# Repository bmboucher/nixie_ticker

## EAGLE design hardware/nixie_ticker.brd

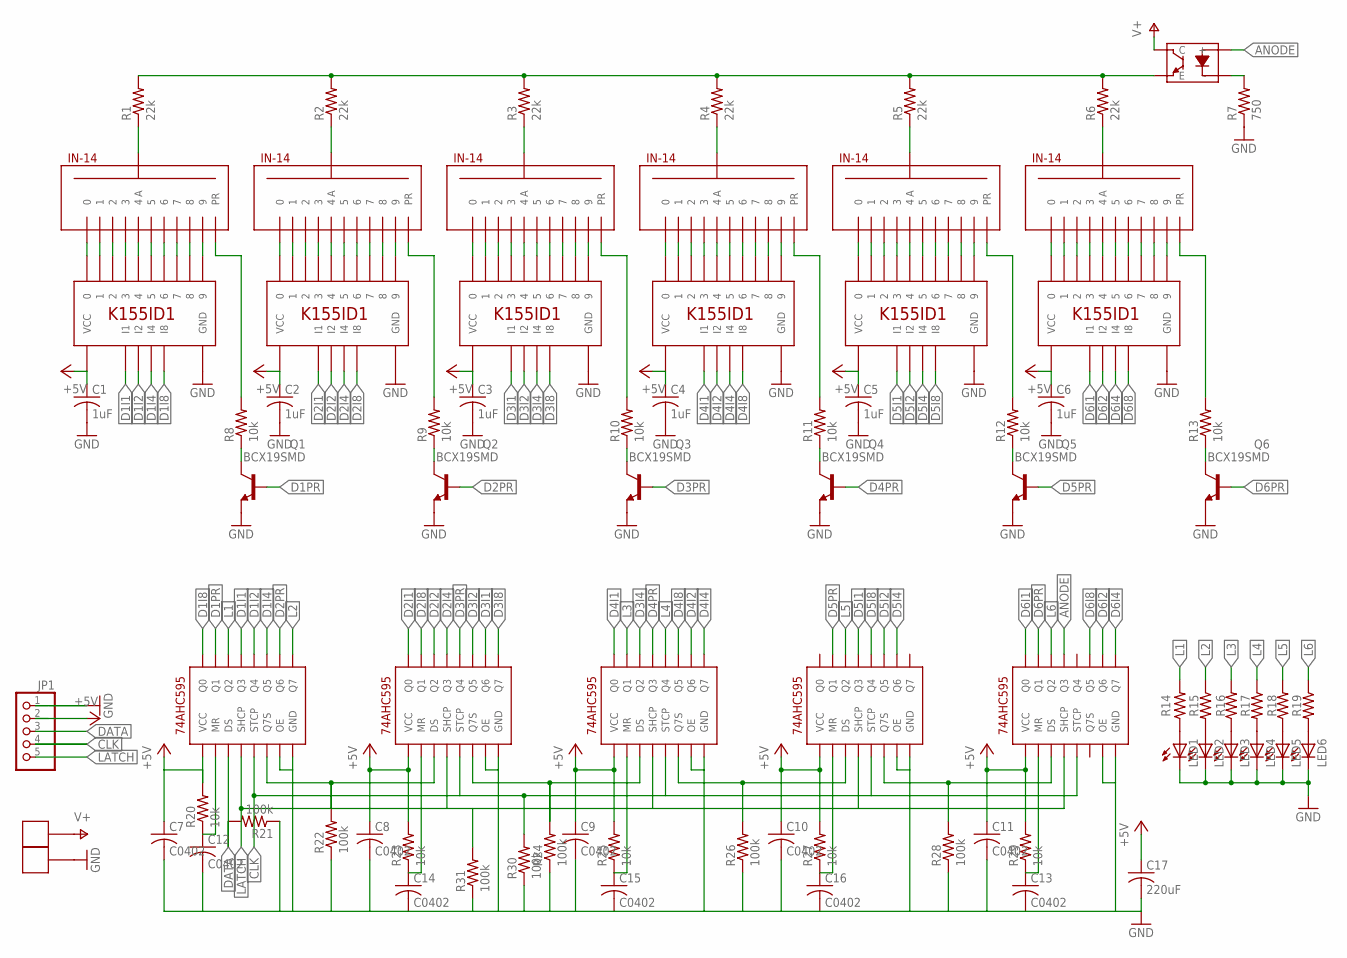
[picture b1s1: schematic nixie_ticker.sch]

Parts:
C1, C2, C3, C4, C5, C6: 1uF; C0402
C7, C8, C9, C10, C11, C12, C13, C14, C15, C16: C0402
C17: 220uF; CAPAE830X1050
JP1: PINHD-1X5; 1X05
JP2, JP3: ZKFDS
LED1, LED2, LED3, LED4, LED5, LED6: LEDCHIP-LED0603; CHIP-LED0603
N1, N2, N3, N4, N5, N6: IN14_12PIN12PIN; IN14-12PIN
Q1, Q2, Q3, Q4, Q5, Q6: BCX19SMD; SOT23-BEC
R1, R2, R3, R4, R5, R6: 22k; R1206
R7: 750; R0603
R8, R9, R10, R11, R12, R13: 10k; R0805
R14, R15, R16, R17, R18, R19: R-US_R0805; R0805
R20, R23, R25, R27, R29: 10k; R0402
R21, R22, R24, R26, R28, R30, R31: 100k; R0402
U1: TLP3873D; SOP254P1000X215-4
U2, U3, U4, U5, U6, U7: K155ID1; DIP-16_SMD
U8, U9, U10, U11, U12: 74AHC595; 16SOIC

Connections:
+5V: C1.1 (+), C2.1 (+), C3.1 (+), C4.1 (+), C5.1 (+), C6.1 (+), C7.1 (+), C8.1 (+), C9.1 (+), C10.1 (+), C11.1 (+), C17.1 (+), JP1.2, R20.2, R23.2, R25.2, R27.2, R29.2, U2.P$5 (VCC), U3.P$5 (VCC), U4.P$5 (VCC), U5.P$5 (VCC), U6.P$5 (VCC), U7.P$5 (VCC), U8.P$16 (VCC), U9.P$16 (VCC), U10.P$16 (VCC), U11.P$16 (VCC), U12.P$16 (VCC)
ANODE: U1.1 (+), U12.P$3 (Q3)
CLK: JP1.4, R30.2, U8.P$12 (STCP), U9.P$12 (STCP), U10.P$12 (STCP), U11.P$12 (STCP), U12.P$12 (STCP)
D1I1: U2.P$3 (I1), U8.P$3 (Q3)
D1I2: U2.P$6 (I2), U8.P$4 (Q4)
D1I4: U2.P$7 (I4), U8.P$5 (Q5)
D1I8: U2.P$4 (I8), U8.P$15 (Q0)
D1PR: Q1.B, U8.P$1 (Q1)
D2I1: U3.P$3 (I1), U9.P$15 (Q0)
D2I2: U3.P$6 (I2), U9.P$2 (Q2)
D2I4: U3.P$7 (I4), U9.P$3 (Q3)
D2I8: U3.P$4 (I8), U9.P$1 (Q1)
D2PR: Q2.B, U8.P$6 (Q6)
D3I1: U4.P$3 (I1), U9.P$6 (Q6)
D3I2: U4.P$6 (I2), U9.P$5 (Q5)
D3I4: U4.P$7 (I4), U10.P$2 (Q2)
D3I8: U4.P$4 (I8), U9.P$7 (Q7)
D3PR: Q3.B, U9.P$4 (Q4)
D4I1: U5.P$3 (I1), U10.P$15 (Q0)
D4I2: U5.P$6 (I2), U10.P$6 (Q6)
D4I4: U5.P$7 (I4), U10.P$7 (Q7)
D4I8: U5.P$4 (I8), U10.P$5 (Q5)
D4PR: Q4.B, U10.P$3 (Q3)
D5I1: U6.P$3 (I1), U11.P$3 (Q3)
D5I2: U6.P$6 (I2), U11.P$5 (Q5)
D5I4: U6.P$7 (I4), U11.P$6 (Q6)
D5I8: U6.P$4 (I8), U11.P$4 (Q4)
D5PR: Q5.B, U11.P$1 (Q1)
D6I1: U7.P$3 (I1), U12.P$15 (Q0)
D6I2: U7.P$6 (I2), U12.P$6 (Q6)
D6I4: U7.P$7 (I4), U12.P$7 (Q7)
D6I8: U7.P$4 (I8), U12.P$5 (Q5)
D6PR: Q6.B, U12.P$1 (Q1)
DATA: JP1.3, R21.2, U8.P$14 (DS)
GND: C1.2 (-), C2.2 (-), C3.2 (-), C4.2 (-), C5.2 (-), C6.2 (-), C7.2 (-), C8.2 (-), C9.2 (-), C10.2 (-), C11.2 (-), C12.2 (-), C13.2 (-), C14.2 (-), C15.2 (-), C16.2 (-), C17.2 (-), JP1.1, JP3.P$1, JP3.P$2, LED1.C, LED2.C, LED3.C, LED4.C, LED5.C, LED6.C, Q1.E, Q2.E, Q3.E, Q4.E, Q5.E, Q6.E, R7.1, R21.1, R22.1, R24.1, R26.1, R28.1, R30.1, R31.1, U2.P$12 (GND), U3.P$12 (GND), U4.P$12 (GND), U5.P$12 (GND), U6.P$12 (GND), U7.P$12 (GND), U8.P$8 (GND), U8.P$13 (OE), U9.P$8 (GND), U9.P$13 (OE), U10.P$8 (GND), U10.P$13 (OE), U11.P$8 (GND), U11.P$13 (OE), U12.P$8 (GND), U12.P$13 (OE)
L1: R14.2, U8.P$2 (Q2)
L2: R15.1, U8.P$7 (Q7)
L3: R16.2, U10.P$1 (Q1)
L4: R17.1, U10.P$4 (Q4)
L5: R18.2, U11.P$2 (Q2)
L6: R19.1, U12.P$2 (Q2)
LATCH: JP1.5, R31.2, U8.P$11 (SHCP), U9.P$11 (SHCP), U10.P$11 (SHCP), U11.P$11 (SHCP), U12.P$11 (SHCP)
unnamed: N1.P$12 (0), U2.P$16 (0)
unnamed: N1.P$3 (1), U2.P$15 (1)
unnamed: N1.P$4 (2), U2.P$8 (2)
unnamed: N1.P$5 (3), U2.P$9 (3)
unnamed: N1.P$6 (4), U2.P$13 (4)
unnamed: N1.P$7 (5), U2.P$14 (5)
unnamed: N1.P$8 (6), U2.P$11 (6)
unnamed: N1.P$9 (7), U2.P$10 (7)
unnamed: N1.P$10 (8), U2.P$1 (8)
unnamed: N1.P$11 (9), U2.P$2 (9)
unnamed: N2.P$12 (0), U3.P$16 (0)
unnamed: N2.P$3 (1), U3.P$15 (1)
unnamed: N2.P$4 (2), U3.P$8 (2)
unnamed: N2.P$5 (3), U3.P$9 (3)
unnamed: N2.P$6 (4), U3.P$13 (4)
unnamed: N2.P$7 (5), U3.P$14 (5)
unnamed: N2.P$8 (6), U3.P$11 (6)
unnamed: N2.P$9 (7), U3.P$10 (7)
unnamed: N2.P$10 (8), U3.P$1 (8)
unnamed: N2.P$11 (9), U3.P$2 (9)
unnamed: R24.2, U9.P$9 (Q7S), U10.P$14 (DS)
unnamed: R22.2, U8.P$9 (Q7S), U9.P$14 (DS)
unnamed: R26.2, U10.P$9 (Q7S), U11.P$14 (DS)
unnamed: R28.2, U11.P$9 (Q7S), U12.P$14 (DS)
unnamed: LED2.A, R15.2
unnamed: C13.1 (+), R29.1, U12.P$10 (MR)
unnamed: LED3.A, R16.1
unnamed: LED1.A, R14.1
unnamed: LED4.A, R17.2
unnamed: N3.P$12 (0), U4.P$16 (0)
unnamed: N3.P$3 (1), U4.P$15 (1)
unnamed: N3.P$4 (2), U4.P$8 (2)
unnamed: N3.P$5 (3), U4.P$9 (3)
unnamed: N3.P$6 (4), U4.P$13 (4)
unnamed: N3.P$7 (5), U4.P$14 (5)
unnamed: N3.P$8 (6), U4.P$11 (6)
unnamed: N3.P$9 (7), U4.P$10 (7)
unnamed: N3.P$10 (8), U4.P$1 (8)
unnamed: N3.P$11 (9), U4.P$2 (9)
unnamed: LED5.A, R18.1
unnamed: LED6.A, R19.2
unnamed: N1.P$2 (PR), R8.2
unnamed: Q1.C, R8.1
unnamed: N3.P$2 (PR), R10.2
unnamed: Q3.C, R10.1
unnamed: N5.P$2 (PR), R12.2
unnamed: Q5.C, R12.1
unnamed: N6.P$2 (PR), R13.2
unnamed: Q6.C, R13.1
unnamed: N1.P$1 (A), R1.1
unnamed: N4.P$12 (0), U5.P$16 (0)
unnamed: N4.P$3 (1), U5.P$15 (1)
unnamed: N4.P$4 (2), U5.P$8 (2)
unnamed: N4.P$5 (3), U5.P$9 (3)
unnamed: N4.P$6 (4), U5.P$13 (4)
unnamed: N4.P$7 (5), U5.P$14 (5)
unnamed: N4.P$8 (6), U5.P$11 (6)
unnamed: N4.P$9 (7), U5.P$10 (7)
unnamed: N4.P$10 (8), U5.P$1 (8)
unnamed: N4.P$11 (9), U5.P$2 (9)
unnamed: N5.P$1 (A), R5.1
unnamed: N5.P$12 (0), U6.P$16 (0)
unnamed: N5.P$3 (1), U6.P$15 (1)
unnamed: N5.P$4 (2), U6.P$8 (2)
unnamed: N5.P$5 (3), U6.P$9 (3)
unnamed: N5.P$6 (4), U6.P$13 (4)
unnamed: N5.P$7 (5), U6.P$14 (5)
unnamed: N5.P$8 (6), U6.P$11 (6)
unnamed: N5.P$9 (7), U6.P$10 (7)
unnamed: N5.P$10 (8), U6.P$1 (8)
unnamed: N5.P$11 (9), U6.P$2 (9)
unnamed: R1.2, R2.2, R3.2, R4.2, R5.2, R6.2, U1.3 (E)
unnamed: R7.2, U1.2 (-)
unnamed: N6.P$1 (A), R6.1
unnamed: N2.P$1 (A), R2.1
unnamed: C14.1 (+), R23.1, U9.P$10 (MR)
unnamed: C12.1 (+), R20.1, U8.P$10 (MR)
unnamed: C15.1 (+), R25.1, U10.P$10 (MR)
unnamed: C16.1 (+), R27.1, U11.P$10 (MR)
unnamed: N3.P$1 (A), R3.1
unnamed: N6.P$12 (0), U7.P$16 (0)
unnamed: N6.P$3 (1), U7.P$15 (1)
unnamed: N6.P$4 (2), U7.P$8 (2)
unnamed: N6.P$5 (3), U7.P$9 (3)
unnamed: N6.P$6 (4), U7.P$13 (4)
unnamed: N6.P$7 (5), U7.P$14 (5)
unnamed: N6.P$8 (6), U7.P$11 (6)
unnamed: N6.P$9 (7), U7.P$10 (7)
unnamed: N6.P$10 (8), U7.P$1 (8)
unnamed: N6.P$11 (9), U7.P$2 (9)
unnamed: N4.P$1 (A), R4.1
unnamed: Q2.C, R9.1
unnamed: Q4.C, R11.1
unnamed: N4.P$2 (PR), R11.2
unnamed: N2.P$2 (PR), R9.2
V+: JP2.P$1, JP2.P$2, U1.4 (C)

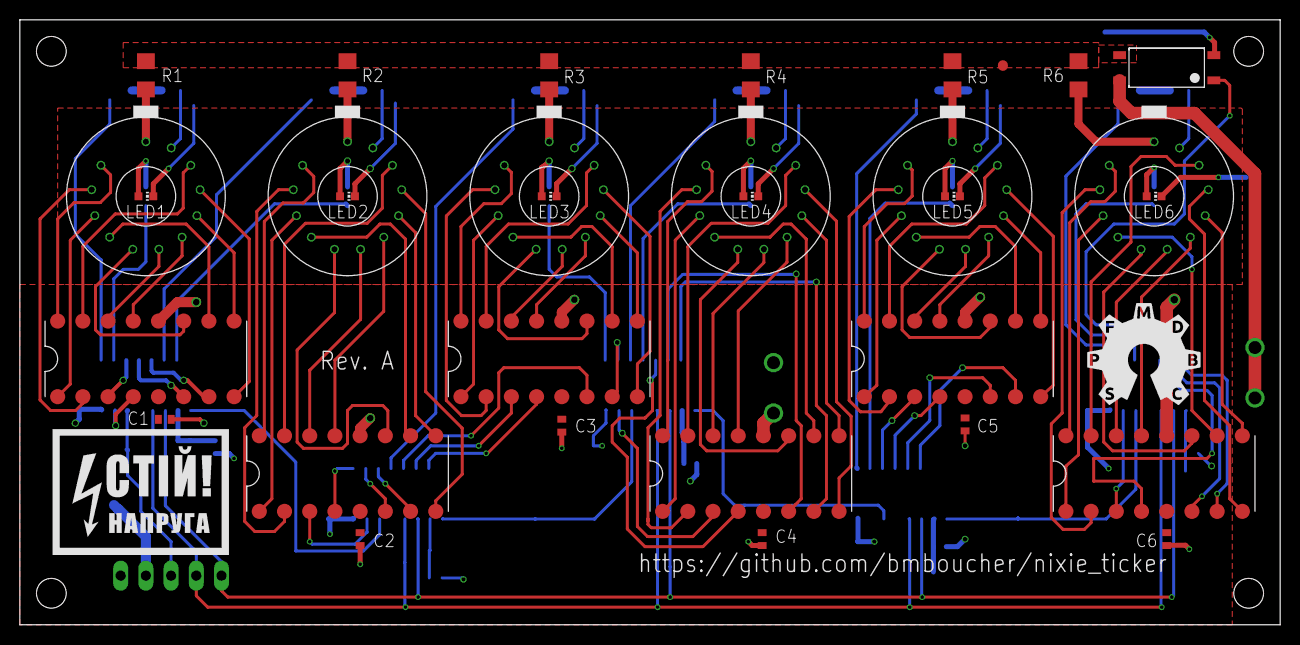
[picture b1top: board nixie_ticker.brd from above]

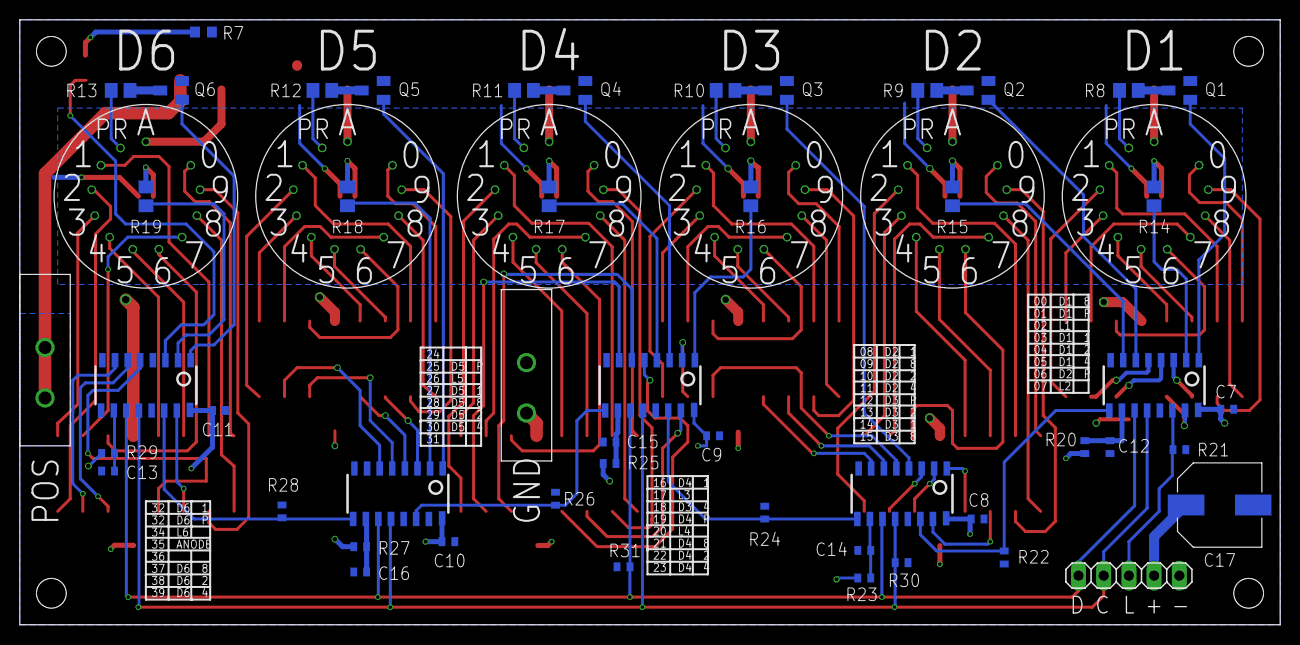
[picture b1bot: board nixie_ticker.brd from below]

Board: 2 copper layers, 127.0 x 61.0 mm, 81 parts (50 on the bottom side), 138 nets.

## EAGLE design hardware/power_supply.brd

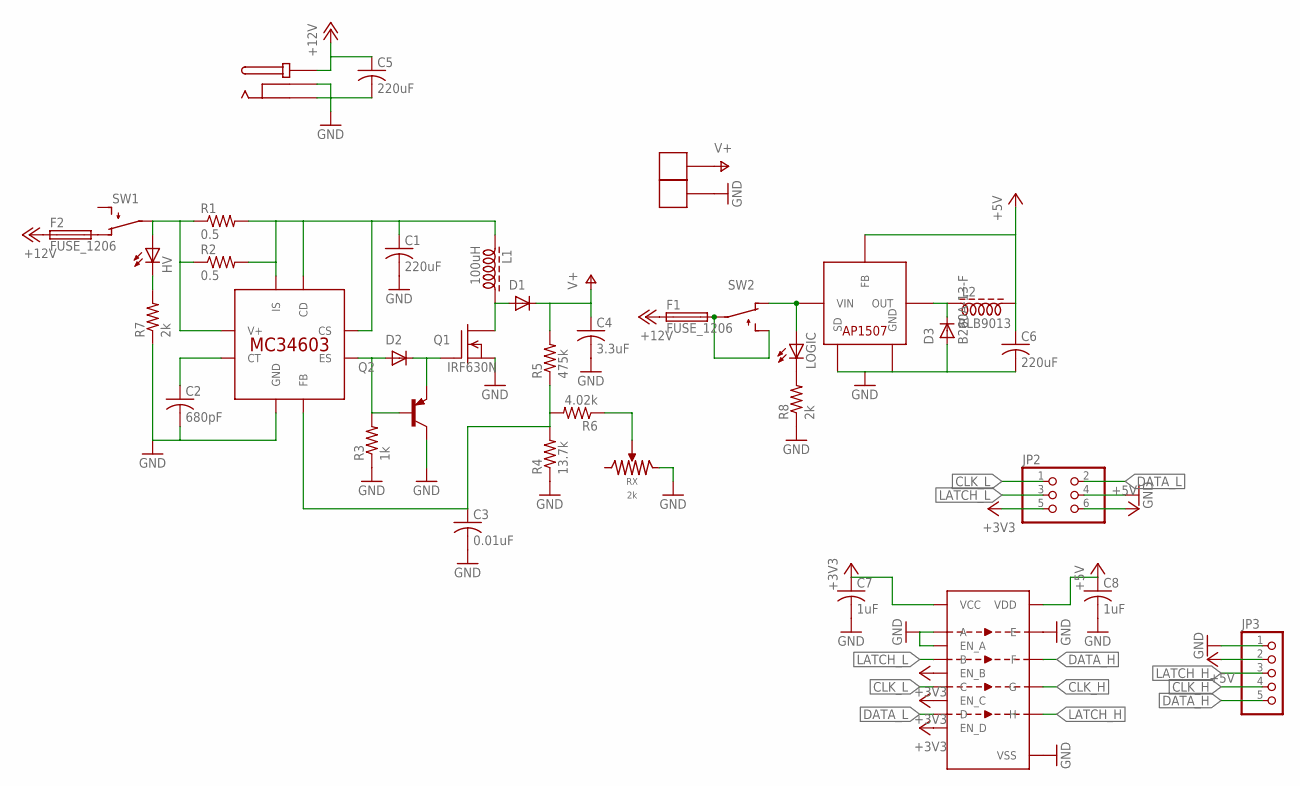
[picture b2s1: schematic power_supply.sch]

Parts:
C1, C5, C6: 220uF; CAPAE830X1050
C2: 680pF; C0402
C3: 0.01uF; C0402
C4: 3.3uF; CAPAE830X1050
C7, C8: 1uF; C0402
D1: BAV21W; SOD3616X115
D2: MMBD914L; SOT23
D3: B260A-13-F; DIOM4326X230
F1, F2: FUSE_1206; R1206
HV: LEDCHIP-LED0805; CHIP-LED0805
JP2: PINHD-2X3; 2X03
JP3: PINHD-1X5; 1X05
L1: 100uH; RLB9012
L2: RLB9013
LOGIC: LEDCHIP-LED0805; CHIP-LED0805
Q1: IRF630N; TO254P1524X483-3
Q2: BC807-16-PNP-SOT23-BEC; SOT23-BEC
R1, R2: 0.5; R1206
R3: 1k; R0805
R4: 13.7k; R1206
R5: 475k; R1206
R6: 4.02k; R1206
R7, R8: 2k; R0805
RX: 2k; TC33X-2
SW1, SW2: T411001B
U1: MC34063; SOIC127P600X175-8
U2: AP1507SOIC-8; SOIC127P600X175-8
U3: CD40109B_SPLITEN; SOP65P640X120-16
U$1: EJ508A
U$5, U$6: ZKFDS

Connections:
+3V3: C7.1 (+), JP2.5, U3.1 (VCC), U3.7 (EN_B), U3.9 (EN_C), U3.15 (EN_D)
+5V: C6.1 (+), C8.1 (+), JP2.6, JP3.2, L2.P$2 (2), U2.3 (FB), U3.16 (VDD)
+12V: C5.1 (+), F1.1, F2.1, U$1.P$1
CLK_H: JP3.4, U3.11 (G)
CLK_L: JP2.1, U3.10 (C)
DATA_H: JP3.5, U3.5 (F)
DATA_L: JP2.2, U3.14 (D)
GND: C1.2 (-), C2.2 (-), C3.2 (-), C4.2 (-), C5.2 (-), C6.2 (-), C7.2 (-), C8.2 (-), D3.2 (A), JP2.4, JP3.1, Q1.2 (S), Q2.C, R3.1, R4.1, R7.1, R8.1, RX.P$3, U1.4 (GND), U2.4 (SD), U2.5 (GND), U2.6 (GND), U2.7 (GND), U2.8 (GND), U3.2 (EN_A), U3.3 (A), U3.4 (E), U3.8 (VSS), U3.12 (VSS), U$1.P$2, U$1.P$3, U$6.P$1, U$6.P$2
LATCH_H: JP3.3, U3.13 (H)
LATCH_L: JP2.3, U3.6 (B)
unnamed: C1.1 (+), L1.P$1 (1), R1.2, R2.2, U1.1 (CS), U1.7 (IS), U1.8 (CD)
unnamed: D1.1 (A), L1.P$2 (2), Q1.3 (D)
unnamed: R6.1, RX.P$2
unnamed: D2.1 (A), Q2.B, R3.2, U1.2 (ES)
unnamed: D2.3 (C), Q1.1 (G), Q2.E
unnamed: HV.A, R1.1, R2.1, SW1.P$2 (2), U1.6 (V+)
unnamed: C2.1 (+), U1.3 (CT)
unnamed: LOGIC.A, SW2.P$1 (1), U2.1 (VIN)
unnamed: C3.1 (+), R4.2, R5.1, R6.2, U1.5 (FB)
unnamed: D3.1 (C), L2.P$1 (1), U2.2 (OUT)
unnamed: HV.C, R7.2
unnamed: LOGIC.C, R8.2
unnamed: F1.2, SW2.P$2 (2), SW2.P$3 (3)
unnamed: F2.2, SW1.P$1 (1)
V+: C4.1 (+), D1.2 (C), R5.2, U$5.P$1, U$5.P$2

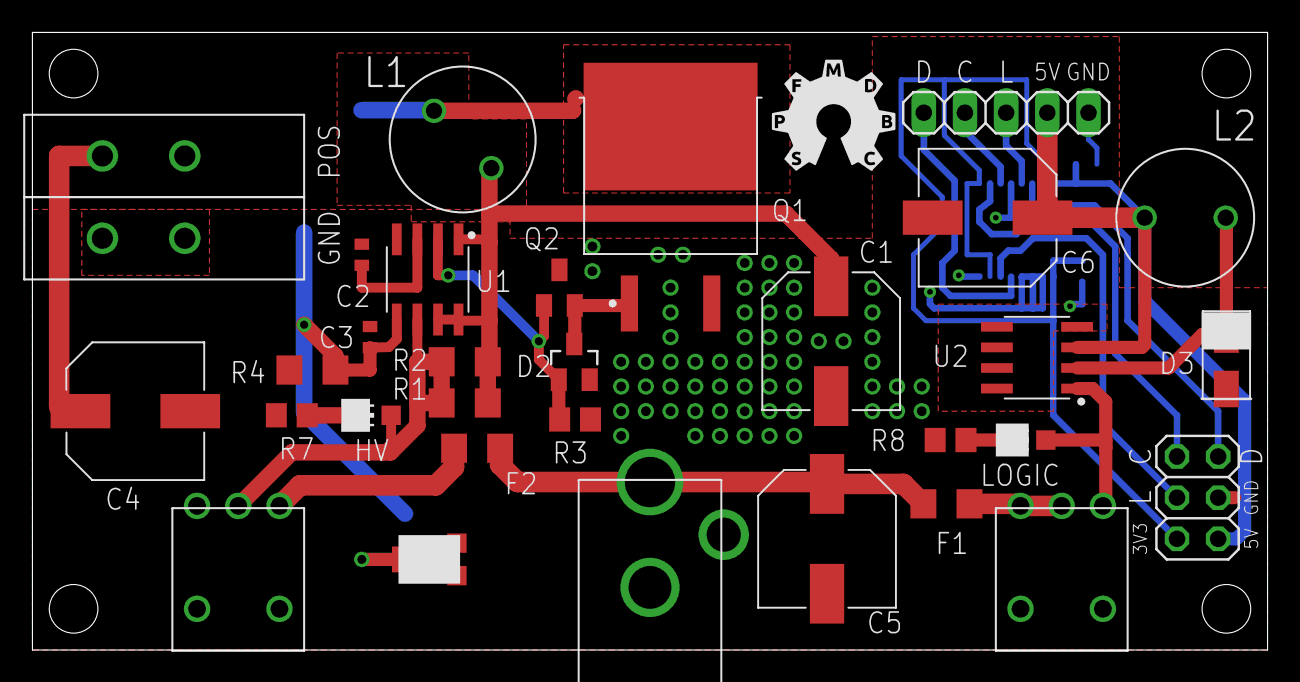
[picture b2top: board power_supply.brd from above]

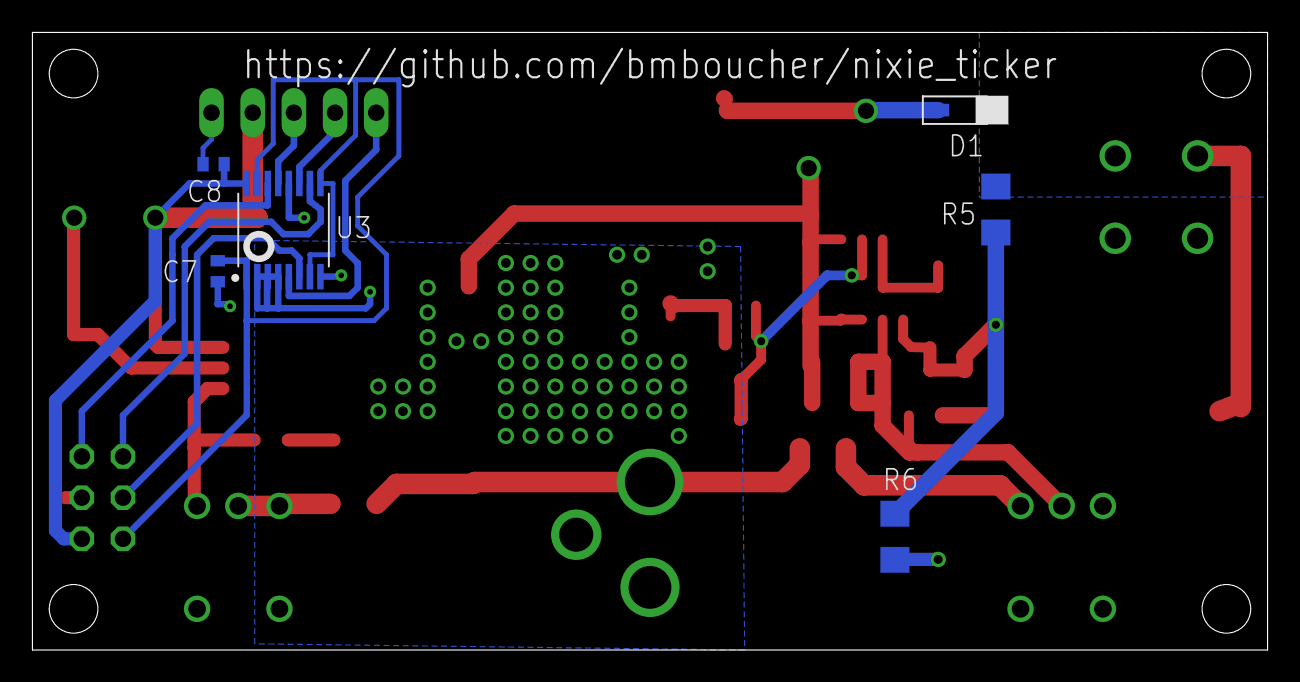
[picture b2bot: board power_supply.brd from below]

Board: 2 copper layers, 76.2 x 38.1 mm, 38 parts (6 on the bottom side), 25 nets.

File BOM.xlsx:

Name | Description | Digikey | Manufacturer | Package | Notes
Power Supply
LED1,LED2 | Green LED | 160-1423-1-ND | LTST-C171GKT | 0805 | 2.1V forward, use 2k resistor for 5mA
R1,R2 | 0.47 Ohm, 1/4W, 5% Resistor | 73L4R47JCT-ND | 73L4R47J | 1206
R3 | 1 kOhm, 1/3W, 5% Resistor | A126435DKR-ND | CRGH0805J1K0 | 0805
R4 | 13.7kOhm, 1/4W, 1% Resistor | RHM13.7KCJCT-ND | MCR18ERTF1372 | 1206
R5 | 475kOhm, 1/4W, 1% Resistor | RMCF1206FG475KCT-ND | RMCF1206FG475K | 1206
R6 | 4.02kOhm, 1/4W, 1% Resistor | RHM4.02KCJCT-ND | MCR18ERTF4021 | 1206
R7,R8 | 2kOhm, 1/8W, 5% Resistor | RMCF0805JT2K00CT-ND | RMCF0805JT2K00 | 0805
RX | 2kOhm Trimmer Pot | 3309P-202-ND | 3309P-1-202 | Through hole
C1,C5,C6 | 220uF, 25V electrolytic cap | 493-2192-1-ND | UWT1E221MNL1GS | 8x10
C2 | 680pF, 50V ceramic cap | 732-7555-1-ND | 885012205060 | 0402
C3 | 0.01uF, 50V ceramic cap | 732-7562-1-ND | 885012205067 | 0402
C4 | 3.3uF, 250V electrolytic cap | 493-9981-1-ND | UUX2E3R3MNL1GS | 8x10
C7,C8 | 1uF, 10V ceramic cap | 445-7368-1-ND | C1005X6S1A105K050BC | 0402
D1 | 250V 50nS rectifier diode | BAV21WRHGCT-ND | BAV21W RHG | SOD-123F
D2 | 100V gen purpose diode | MMBD914LT1GOSCT-ND | MMBD914LT1G | SOT-23-3
D3 | 60V schottky diode | B260A-FDICT-ND | B260A-13-F | SMA | Already bought
Q1 | 200V N-channel MOSFET | IRF630NSTRLPBFCT-ND | IRF630NSTRLPBF | D2PAK
Q2 | 65V PNP Transistor | BC856BLT3GOSCT-ND | BC856BLT3G | SOT-23-3
U1 | IC Boost Regulator | MC34063ADGOS-ND | MC34063ADG | 8-SOIC
U2 | IC 5V Buck Regulator | 1034-AP1507-50D5LDICT-ND | AP1507-50D5L-13 | TO-252-5
U3 | Level shifter | 296-12163-1-ND | CD40109BPWR | 16-TSSOP
L1 | 100uH 1.4A inductor | RLB9012-101KL-ND | RLB9012-101KL | Through hole
L2 | 47uH 2.35A inductor | RLB0913-470K-ND | RLB0913-470K | Through hole
SW1,SW2 | Switches | EG4326-ND | 400MSP1R6BLKM6QE | Through hole
Phoenix | Phoenix contact | 277-1316-ND | 1706714 | Through hole
 | Phoenix contact separator | 277-6463-ND | 1870666 |  |  |  | 1E-3
DC Jack | 2.1mm DC power jack | EJ508A-ND | EJ508A | Through hole | Already bought
F1,F2 | 500mA fuse | 507-1876-1-ND | C1F 500

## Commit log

2018-06-27 Adding nixie_ticker library with IN-14 and K155ID1 parts
2018-06-27 Initial placing of nixies and drivers
2018-06-27 Initial routing for first nixie
2018-06-27 Wiring all nixie tubes using design blocks
2018-06-27 Removing grid lines
2018-06-28 Adding high voltage logo
2018-06-28 Adding optocouplers to drive anodes
2018-06-28 Adding high-voltage rail
2018-06-29 Updates 6-29
2018-07-01 Finalizing board 7-1
2018-07-07 Updates 7-7
2018-07-10 Updating power supply 7/10
2018-07-10 Adding box
2018-07-11 Updating power_supply, 7-11
2018-07-11 Adding CAM files
2018-07-16 Updating power_supply
2018-08-12 Updating 8-12
2018-08-12 Changing OSH logo on power supply
2018-08-17 Updates 8-17, adding fifth shift register
2018-08-17 Updates to BOM
2018-08-18 Final update before submitting to PCB shop
2018-08-29 Adding CAD files
2018-08-29 Updates 8-28
2018-08-30 Adding stencil mounts/spacers to CAD
2018-08-30 Adding software
2018-08-30 Turning off binary counter
2018-08-30 Moving .gitignore
2018-08-30 Adding software/bin/.gitignore
2018-08-30 Refactoring software to object-oriented
2018-08-30 Fixing compilation errors in software
2018-08-30 Adding calls to display.update
2018-08-30 Adding log message for test_single_register
2018-08-30 Adding reset to initialization for NixieDisplay
2018-08-30 Changing type of reg in main to int
2018-08-30 Fixing log mesage in test_single_register
2018-08-30 Adding string parsing to software driver
2018-08-30 Adding call to set_anode in NixieDisplay::write
2018-08-30 Adding log messages to NixieDisplay::write
2018-08-30 Replacing std::cin >> with getline
2018-08-30 Fixing compilation error
2018-08-30 Adding led++
2018-08-30 Fixing terminal decimal point in NixieDisplay::write
2018-08-30 Cleaning up log messages
2018-08-30 Fixing unused warning
2018-08-30 More cleanup of log messages
2018-08-30 Adding digit reversal to nixies
2018-08-30 Adding exception to digit reversal for >9 digits
2018-08-30 Adding fix to decimal point location
2018-08-31 Fixing digit reversal for 0/1
2018-08-31 Adding gitignore files for bin/lib/obj
2018-08-31 Updating makefile to make shared library
2018-08-31 Updating makefile and adding nixie_tester.cpp
2018-08-31 Adding src/nixie_tester.cpp
2018-08-31 Moving executable sections to nixie_tester.cpp file
2018-08-31 Updating makefile with -shared flag
2018-08-31 Moving NUM_NIXIES constant to nixie_driver.hpp
2018-08-31 Removing NUM_NIXIES from src/nixie_driver.cpp
2018-08-31 Updating makefile to retain .o files
2018-08-31 Adding nixie_demo
2018-09-01 Adding nixie_clock
2018-09-01 Adding power supply spacers to CAD
2018-09-01 Adding cycling LEDs to nixie_clock
2018-09-05 Adding nixie_ticker executable
2018-09-05 Adding curl test code
2018-09-05 Changing holes in acrylic top
2018-09-05 Adding hinge spacer tool
2018-09-05 Cleaning up nixie_ticker.cpp code, pointing to IEX
2018-09-05 Looping HTTPS request
2018-09-05 Adding custom write_data
2018-09-05 Fixing pointer compilation error
2018-09-05 Adding return in write_data
2018-09-05 Fixing write_data
2018-09-05 Adding flush to write_data
2018-09-05 Adding REQUEST log message
2018-09-05 Adding CURLOPT_WRITEDATA
2018-09-05 Changing CURLOPT_WRITEDATA call to C-style
2018-09-05 Removing REQUEST message
2018-09-05 Cleanup
2018-09-05 Extending delay
2018-09-05 Moving blank spaces to end
2018-09-05 Updating to multiple tickers
2018-09-05 Adding ()
2018-09-05 Adding url printer
2018-09-05 Changing type of current_ticker
2018-09-05 Adding 'Adding tickers' log message
2018-09-05 Adding tickers[0] message
2018-09-05 Casting NUM_NIXIES to size_t
2018-09-05 Printing all tickers
2018-09-05 Removing pre-sizing of tickers
2018-09-05 Printing url again
2018-09-05 changing delay
2018-09-05 Extending TICKER_SWITCH, shortening TICK_DELAY
2018-09-17 Removing name
2018-09-17 Organizing
2018-09-17 Updating .gitignore to remove .cam files
